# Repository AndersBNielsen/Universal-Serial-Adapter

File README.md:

# Universal-Serial-Adapter

## Hackable USB-C UART RS232 Adapter

The **Universal Serial Adapter** is an open-source hardware project designed to bridge USB-C, RS232, and TTL communication. This fully assembled adapter is packed with features tailored for advanced prototyping, embedded development, and system debugging.  

Make one yourself or <a href="https://www.imania.dk/product_info.php?cPath=204&products_id=7224&language=en">buy one here</a>

## **Technical Summary**  

### **Key Features**  
- **USB-C to RS232 Interface**  
  - USB-C (female) connector to DSUB9 RS232 (male) port.  
  - Supports bidirectional communication between modern USB-C devices and RS232 hardware.  

- **TTL Signal Breakouts**  
  - TTL RX, TX, and control signal pins exposed for easy interfacing with UART-based systems.  

- **Signal Polarity Configuration**  
  - RS232 RX, TX, and control signals configurable using 2.54mm header jumpers:  
    - **Horizontal jumper placement**: Straight connection.  
    - **Vertical jumper placement**: Crossed connection.  

- **USB-C Line Breakouts**  
  - Access to USB-C data lines for advanced custom applications.  

- **3.3V Linear Regulator**  
  - Integrated 3.3V linear regulator for powering external circuits.  

### **Core Components**  
- **WCH CH340G**: USB-to-UART bridge IC for reliable USB communication.  
- **SP3243**: TTL-to-RS232 transceiver IC for robust RS232 signaling.  

### **Customization and Modifications**  
- Advanced features such as additional breakout options or alternate configurations may require soldering or cutting traces on the PCB.  
- Preinstalled components include:  
  - USB-C connector  
  - DSUB9 RS232 connector  
  - UART header  
  - Configuration jumper blocks  
- Open to further modification for specific use cases.  

### **Open-Source Design**  
- Designed in **KiCAD 8**, with all source files available for inspection and modification.  
- Licensed under an open-source hardware license, encouraging collaboration and adaptation.  
- Repository includes:  
  - KiCAD design files.  
  - PCB layout and schematics.  
  - Bill of Materials (BOM).  

### **Applications**  
- Embedded system development.  
- Debugging and diagnostics of RS232 hardware.  
- Bridging modern USB-C devices to legacy RS232 systems.  

## **Repository Contents**  
- **/hardware/**: KiCAD project files for the PCB.  

## **Important Notes**  
- This adapter is a professional-grade tool and may require advanced soldering and modification skills for some features.  
- Enclosures, cables, and other accessories are not included.  

## **Get Started**  
Clone or download the repository to start customizing:  
```bash  
git clone https://github.com/AndersBNielsen/Universal-Serial-Adapter.git  
```
## Getting a PCB
This project is kindly sponsored by JLCPCB. They offer cheap, professional looking PCBs and super fast delivery.

Step 1: Get the gerber file zip package from the /hardware folder

Step 2: Upload to JLCPCB [https://jlcpcb.com](https://jlcpcb.com/?from=Anders_N)

Step 3: Pick your color, surface finish and order.

If you want JLCPCB to assemble a board, the BOM and placement files are also in the repo. 

You can use these affiliate links to get a board for $2 and also get $60 worth of New User Coupons at: https://jlcpcb.com/?from=Anders_N

And in case you also want to order a 3D-printed case you can use this link. 
How to Get a $7 3D Printing Coupon: https://jlc3dp.com/?from=Anders_N

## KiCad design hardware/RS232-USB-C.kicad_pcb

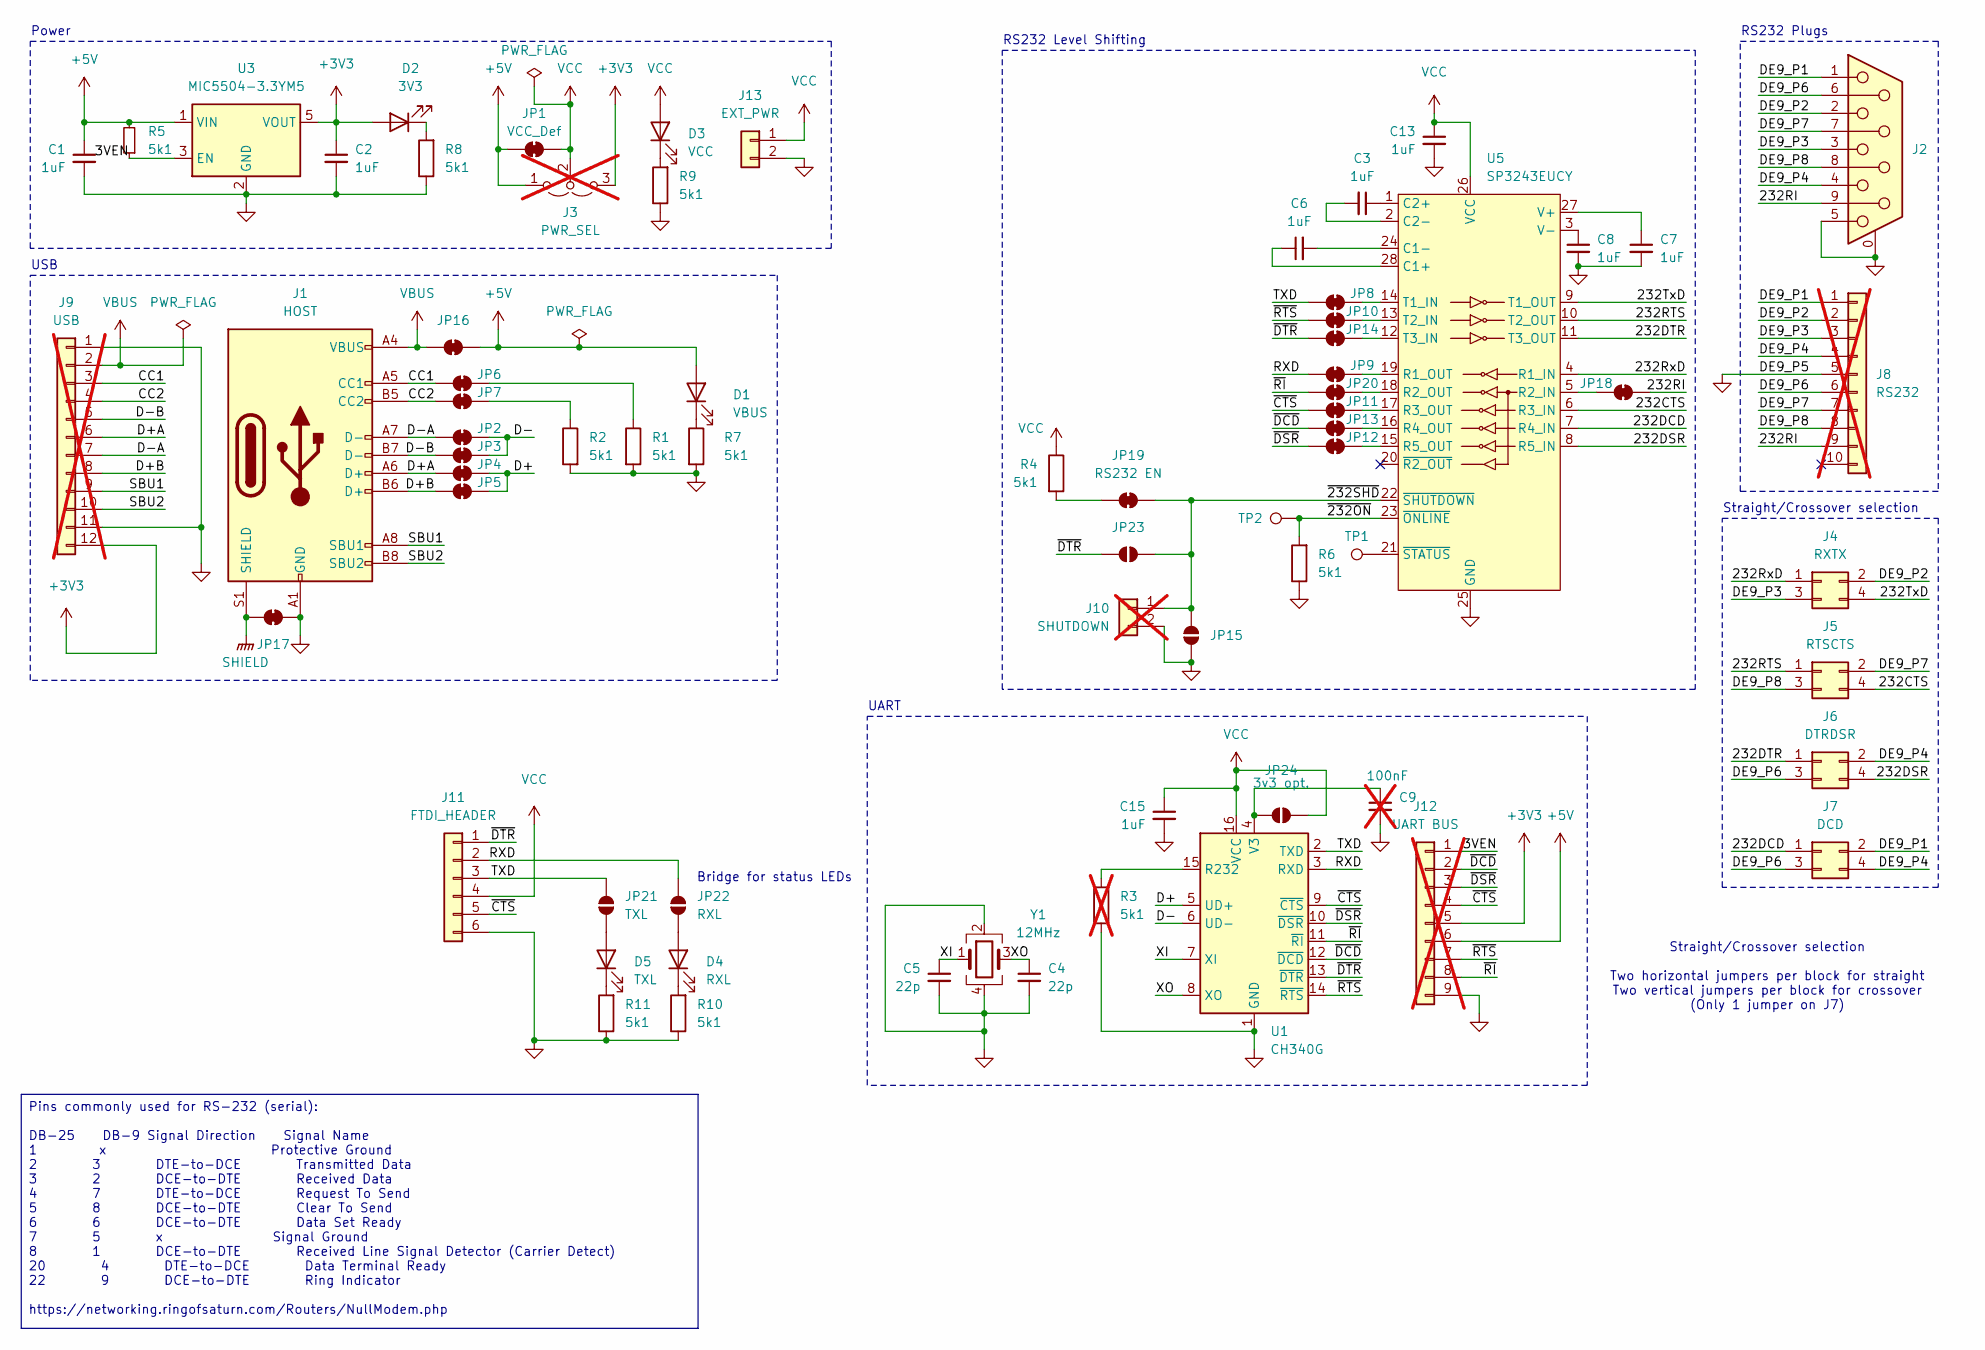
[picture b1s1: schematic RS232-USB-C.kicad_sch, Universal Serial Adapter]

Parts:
C1, C2, C3, C6, C7, C8, C13, C15: 1uF; C_0805_2012Metric; LCSC C28323
C4, C5: 22p; C_0805_2012Metric
C9: 100nF; C_0805_2012Metric; LCSC C28323; not fitted
D1: VBUS; LED_0603_1608Metric; LCSC C2286
D2: 3V3; LED_0603_1608Metric; LCSC C2286
D3: VCC; LED_0603_1608Metric; LCSC C2286
D4: RXL; LED_0603_1608Metric; LCSC C2286
D5: TXL; LED_0603_1608Metric; LCSC C2286
J1: HOST; USB_C_Receptacle_HCTL_HC-TYPE-C-16P-01A; LCSC C2894897
J2: DE9_Receptacle; DSUB-9_Female_Horizontal_P2.77x2.84mm_EdgePinOffset7.70mm_H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; LCSC C19077344
J3: PWR_SEL; PinHeader_1x03_P2.54mm_Vertical; not fitted
J4: RXTX; PinHeader_2x02_P2.54mm_Vertical; LCSC C492419
J5: RTSCTS; PinHeader_2x02_P2.54mm_Vertical; LCSC C492419
J6: DTRDSR; PinHeader_2x02_P2.54mm_Vertical; LCSC C492419
J7: DCD; PinHeader_2x02_P2.54mm_Vertical; LCSC C492419
J8: RS232; PinHeader_2x05_P2.54mm_Vertical; not fitted
J9: USB; PinHeader_2x06_P2.54mm_Vertical; not fitted
J10: SHUTDOWN; PinHeader_1x02_P2.54mm_Vertical; not fitted
J11: FTDI_HEADER; PinHeader_1x06_P2.54mm_Vertical; LCSC C37208
J12: UART BUS; PinHeader_1x09_P2.54mm_Vertical; not fitted
J13: EXT_PWR; PinHeader_1x02_P2.54mm_Vertical
JP1: VCC_Def; SolderJumper-2_P1.3mm_Bridged_RoundedPad1.0x1.5mm
JP2: A7; SolderJumper-2_P1.3mm_Bridged_RoundedPad1.0x1.5mm
JP3: B7; SolderJumper-2_P1.3mm_Bridged_RoundedPad1.0x1.5mm
JP4: A6; SolderJumper-2_P1.3mm_Bridged_RoundedPad1.0x1.5mm
JP5: B6; SolderJumper-2_P1.3mm_Bridged_RoundedPad1.0x1.5mm
JP6: CC1/A5; SolderJumper-2_P1.3mm_Bridged_RoundedPad1.0x1.5mm
JP7: CC2/B5; SolderJumper-2_P1.3mm_Bridged_RoundedPad1.0x1.5mm
JP8: TXD; SolderJumper-2_P1.3mm_Bridged_RoundedPad1.0x1.5mm
JP9: RXD; SolderJumper-2_P1.3mm_Bridged_RoundedPad1.0x1.5mm
JP10: RTS; SolderJumper-2_P1.3mm_Bridged_RoundedPad1.0x1.5mm
JP11: CTS; SolderJumper-2_P1.3mm_Bridged_RoundedPad1.0x1.5mm
JP12: DSR; SolderJumper-2_P1.3mm_Bridged_RoundedPad1.0x1.5mm
JP13: DCD; SolderJumper-2_P1.3mm_Bridged_RoundedPad1.0x1.5mm
JP14: DTR; SolderJumper-2_P1.3mm_Bridged_RoundedPad1.0x1.5mm
JP15, JP23: RS232 Shutdown; SolderJumper-2_P1.3mm_Open_RoundedPad1.0x1.5mm
JP16: VBUS; SolderJumper-2_P1.3mm_Bridged_RoundedPad1.0x1.5mm
JP17: Shield; SolderJumper-2_P1.3mm_Bridged_RoundedPad1.0x1.5mm
JP18: 232RI; SolderJumper-2_P1.3mm_Bridged_RoundedPad1.0x1.5mm
JP19: RS232 EN; SolderJumper-2_P1.3mm_Bridged_RoundedPad1.0x1.5mm
JP20: RI; SolderJumper-2_P1.3mm_Bridged_RoundedPad1.0x1.5mm
JP21: TXL; SolderJumper-2_P1.3mm_Open_RoundedPad1.0x1.5mm
JP22: RXL; SolderJumper-2_P1.3mm_Open_RoundedPad1.0x1.5mm
JP24: 3v3 opt.; SolderJumper-2_P1.3mm_Open_RoundedPad1.0x1.5mm
R1, R2, R4, R5, R6, R7, R8, R9, R10, R11: 5k1; R_0805_2012Metric
R3: 5k1; R_0805_2012Metric; not fitted
TP1, TP2: TestPoint; TestPoint_Pad_D1.0mm
U1: CH340G; SOIC-16_3.9x9.9mm_P1.27mm; LCSC C14267
U3: MIC5504-3.3YM5; SOT-23-5; LCSC C2832127
U5: SP3243EUCY; SSOP-28_5.3x10.2mm_P0.65mm; LCSC C916165
Y1: 12MHz; Crystal_SMD_3225-4Pin_3.2x2.5mm; LCSC C133334

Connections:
+3V3: C2.1, D2.2 (A), J3.3 (B), J9.12, J12.5, U3.5 (VOUT)
+5V: C1.1, D1.2 (A), J3.1 (A), J12.6, JP1.1 (A), JP16.2 (B), R5.2, U3.1 (VIN)
/3VEN: J12.1, R5.1, U3.3 (EN)
/232CTS: J5.4, U5.6 (R3_IN)
/232DCD: J7.1, U5.7 (R4_IN)
/232DSR: J6.4, U5.8 (R5_IN)
/232DTR: J6.1, U5.11 (T3_OUT)
/232RI: J2.9, J8.9, JP18.2 (B)
/232RTS: J5.1, U5.10 (T2_OUT)
/232RxD: J4.1, U5.4 (R1_IN)
/232TxD: J4.4, U5.9 (T1_OUT)
/CC1: J1.A5 (CC1), J9.3, JP6.1 (A)
/CC2: J1.B5 (CC2), J9.4, JP7.2 (B)
/D+: JP4.2 (B), JP5.2 (B), U1.5 (UD+)
/D+A: J1.A6 (D+), J9.6, JP4.1 (A)
/D+B: J1.B6 (D+), J9.8, JP5.1 (A)
/D-: JP2.2 (B), JP3.2 (B), U1.6 (UD-)
/D-A: J1.A7 (D-), J9.7, JP2.1 (A)
/D-B: J1.B7 (D-), J9.5, JP3.1 (A)
/DE9_P1: J2.1, J7.2, J8.1
/DE9_P2: J2.2, J4.2, J8.2
/DE9_P3: J2.3, J4.3, J8.3
/DE9_P4: J2.4, J6.2, J7.4, J8.4
/DE9_P6: J2.6, J6.3, J7.3, J8.6
/DE9_P7: J2.7, J5.2, J8.7
/DE9_P8: J2.8, J5.3, J8.8
/RXD: J11.2, JP9.1 (A), JP22.1 (A), U1.3 (RXD)
/SBU1: J1.A8 (SBU1), J9.9
/SBU2: J1.B8 (SBU2), J9.10
/TXD: J11.3, JP8.1 (A), JP21.1 (A), U1.2 (TXD)
/XI: C5.1, U1.7 (XI), Y1.1
/XO: C4.1, U1.8 (XO), Y1.3
/~232ON: R6.2, TP2.1, U5.23 (~ONLINE)
/~232SHD: J10.1, JP15.2 (B), JP19.2 (B), JP23.1 (A), U5.22 (~SHUTDOWN)
/~CTS: J11.5, J12.4, JP11.1 (A), U1.9 (~CTS)
/~DCD: J12.2, JP13.1 (A), U1.12 (~DCD)
/~DSR: J12.3, JP12.1 (A), U1.10 (~DSR)
/~DTR: J11.1, JP14.1 (A), JP23.2 (B), U1.13 (~DTR)
/~RI: J12.8, JP20.1 (A), U1.11 (~RI)
/~RTS: J12.7, JP10.1 (A), U1.14 (~RTS)
GND: C1.2, C2.2, C4.2, C5.2, C7.2, C8.2, C9.2, C13.2, C15.2, J1.A1 (GND), J1.A12 (GND), J1.B1 (GND), J1.B12 (GND), J2.0 (PAD), J2.5, J8.5, J9.1, J9.11, J10.2, J11.6, J12.9, J13.2, JP15.1 (A), JP17.2 (B), R1.2, R2.2, R3.1, R6.1, R7.2, R8.1, R9.1, R10.1, R11.1, U1.1 (GND), U3.2 (GND), U5.25 (GND), Y1.2, Y1.4
unnamed: D1.1 (K), R7.1
unnamed: D2.1 (K), R8.2
unnamed: D3.1 (K), R9.2
unnamed: D4.2 (A), JP22.2 (B)
unnamed: D4.1 (K), R10.2
unnamed: D5.2 (A), JP21.2 (B)
unnamed: D5.1 (K), R11.2
unnamed: JP6.2 (B), R1.1
unnamed: JP7.1 (A), R2.1
unnamed: JP8.2 (B), U5.14 (T1_IN)
unnamed: JP9.2 (B), U5.19 (R1_OUT)
unnamed: JP10.2 (B), U5.13 (T2_IN)
unnamed: JP11.2 (B), U5.17 (R3_OUT)
unnamed: JP12.2 (B), U5.15 (R5_OUT)
unnamed: JP13.2 (B), U5.16 (R4_OUT)
unnamed: JP14.2 (B), U5.12 (T3_IN)
unnamed: JP18.1 (A), U5.5 (R2_IN)
unnamed: JP19.1 (A), R4.2
unnamed: JP20.2 (B), U5.18 (R2_OUT)
unnamed: C9.1, JP24.1 (A), U1.4 (V3)
unnamed: R3.2, U1.15 (R232)
unnamed: C6.1, U5.28 (C1+)
unnamed: C6.2, U5.24 (C1-)
unnamed: C3.1, U5.1 (C2+)
unnamed: C3.2, U5.2 (C2-)
unnamed: C7.1, U5.27 (V+)
unnamed: C8.1, U5.3 (V-)
unnamed: TP1.1, U5.21 (~STATUS)
SHIELD: J1.S1 (SHIELD), JP17.1 (A)
VBUS: J1.A4 (VBUS), J1.A9 (VBUS), J1.B4 (VBUS), J1.B9 (VBUS), J9.2, JP16.1 (A)
VCC: C13.1, C15.1, D3.2 (A), J3.2 (C), J11.4, J13.1, JP1.2 (B), JP24.2 (B), R4.1, U1.16 (VCC), U5.26 (VCC)

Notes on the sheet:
Bridge for status LEDs
Power
RS232 Plugs
Straight/Crossover selection Two horizontal jumpers per block for straight Two vertical jumpers per block for crossover (Only 1 jumper on J7)
UART
USB
Straight/Crossover selection
RS232 Level Shifting
Pins commonly used for RS-232 (serial): DB-25 DB-9 Signal Direction Signal Name 1 x Protective Ground 2 3 DTE-to-DCE Transmitted Data 3 2 DCE-to-DTE Received Data 4 7 DTE-to-DCE Request To Send 5 8 DCE-to-DTE Clear To Send 6 6 DCE-to-DTE Data Set Ready 7 5 x Signal Ground 8 1 DCE-to-DTE Received Li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

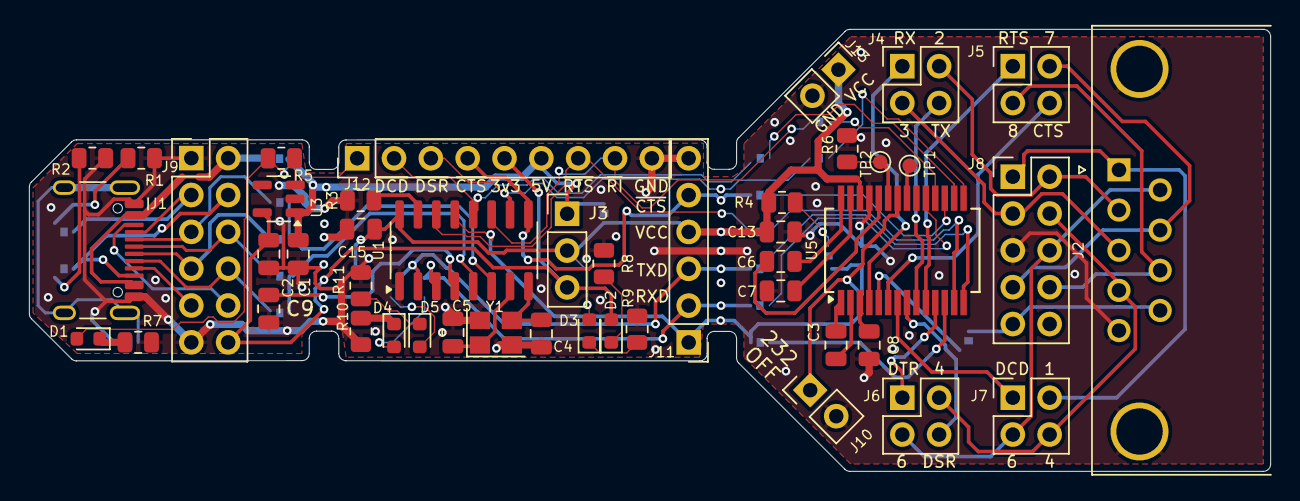
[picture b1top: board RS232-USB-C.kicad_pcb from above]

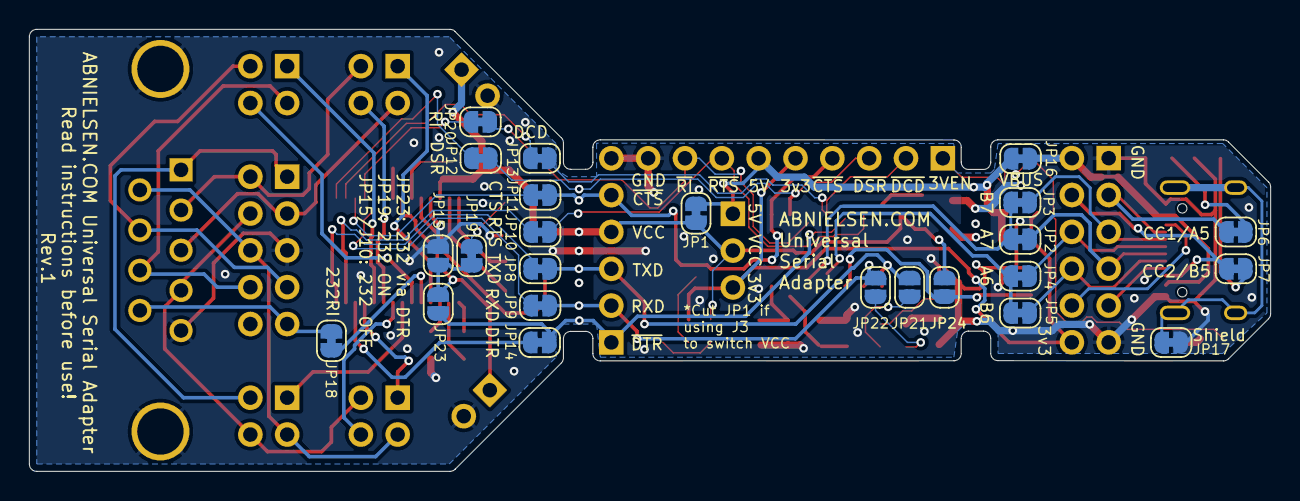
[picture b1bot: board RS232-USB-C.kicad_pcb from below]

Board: 2 copper layers, 85.6 x 30.5 mm, 70 parts (24 on the bottom side), 72 nets.

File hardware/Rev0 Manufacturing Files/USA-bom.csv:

"Reference","Value","Datasheet","Footprint","Qty","DNP","LCSC"
"C1,C2,C3,C6,C7,C8,C13,C15","1uF","~","Capacitor_SMD:C_0805_2012Metric","8","","C28323"
"C4,C5","22p","~","Capacitor_SMD:C_0805_2012Metric","2","",""
"D1","VBUS","~","LED_SMD:LED_0603_1608Metric","1","","C2286"
"D2","3V3","~","LED_SMD:LED_0603_1608Metric","1","","C2286"
"D3","VCC","~","LED_SMD:LED_0603_1608Metric","1","","C2286"
"D4","RXL","~","LED_SMD:LED_0603_1608Metric","1","","C2286"
"D5","TXL","~","LED_SMD:LED_0603_1608Metric","1","","C2286"
"J1","USB_C_Receptacle_USB2.0_16P","https://www.usb.org/sites/default/files/documents/usb_type-c.zip","Connector_USB:USB_C_Receptacle_HCTL_HC-TYPE-C-16P-01A","1","","C2894897"
"J2","DE9_Receptacle","~","Connector_Dsub:DSUB-9_Female_Horizontal_P2.77x2.84mm_EdgePinOffset7.70mm_Housed_MountingHolesOffset9.12mm","1","","C19077344"
"J3,J8,J9,J10,J12,J13,R3","NC","~","-- mixed values --","7","",""
"J4","RXTX","~","Connector_PinHeader_2.54mm:PinHeader_2x02_P2.54mm_Vertical","1","","C492419"
"J5","RTSCTS","~","Connector_PinHeader_2.54mm:PinHeader_2x02_P2.54mm_Vertical","1","","C492419"
"J6","DTRDSR","~","Connector_PinHeader_2.54mm:PinHeader_2x02_P2.54mm_Vertical","1","","C492419"
"J7","DCD","~","Connector_PinHeader_2.54mm:PinHeader_2x02_P2.54mm_Vertical","1","","C492419"
"J11","UART","~","Connector_PinHeader_2.54mm:PinHeader_1x06_P2.54mm_Vertical","1","",""
"R1,R2,R4,R5,R6,R7,R8,R9,R10,R11","5k1","~","Resistor_SMD:R_0805_2012Metric","10","",""
"TP1,TP2","TestPoint","~","TestPoint:TestPoint_Pad_D1.0mm","2","",""
"U1","CH340G","http://www.datasheet5.com/pdf-local-2195953","Package_SO:SOIC-16_3.9x9.9mm_P1.27mm","1","","C14267"
"U3","MIC5504-3.3YM5","http://ww1.microchip.com/downloads/en/DeviceDoc/MIC550X.pdf","Package_TO_SOT_SMD:SOT-23-5","1","","C2832127"
"U5","SP3243EUCY","","Package_SO:SSOP-28_5.3x10.2mm_P0.65mm","1","","C916165"
"Y1","12MHz","~","Crystal:Crystal_SMD_3225-4Pin_3.2x2.5mm","1","","C133334"

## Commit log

2024-12-18 Photos and schematic PDF
2024-12-20 Tidy schematic
    - Replaced criss-crossed wires with labels between IC/connectors
    - Removed jumper 'values' where wasn't really needed
    - repositioned references/values where hard to read
    - gave components room to 'breathe'
    - changed to regular (compared to small) components in most places to avoid cramping
    - moved components around to be close to their logical section
2024-12-20 Update schematic PDF
2026-03-18 Rev 1

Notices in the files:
hardware/RS232-USB-C.kicad_sch:
License: https://creativecommons.org/licenses/by-sa/4.0
